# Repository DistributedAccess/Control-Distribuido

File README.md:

# Control-Distribuidos
Sistema de control de acceso distribuido por reconocimiento de patrones

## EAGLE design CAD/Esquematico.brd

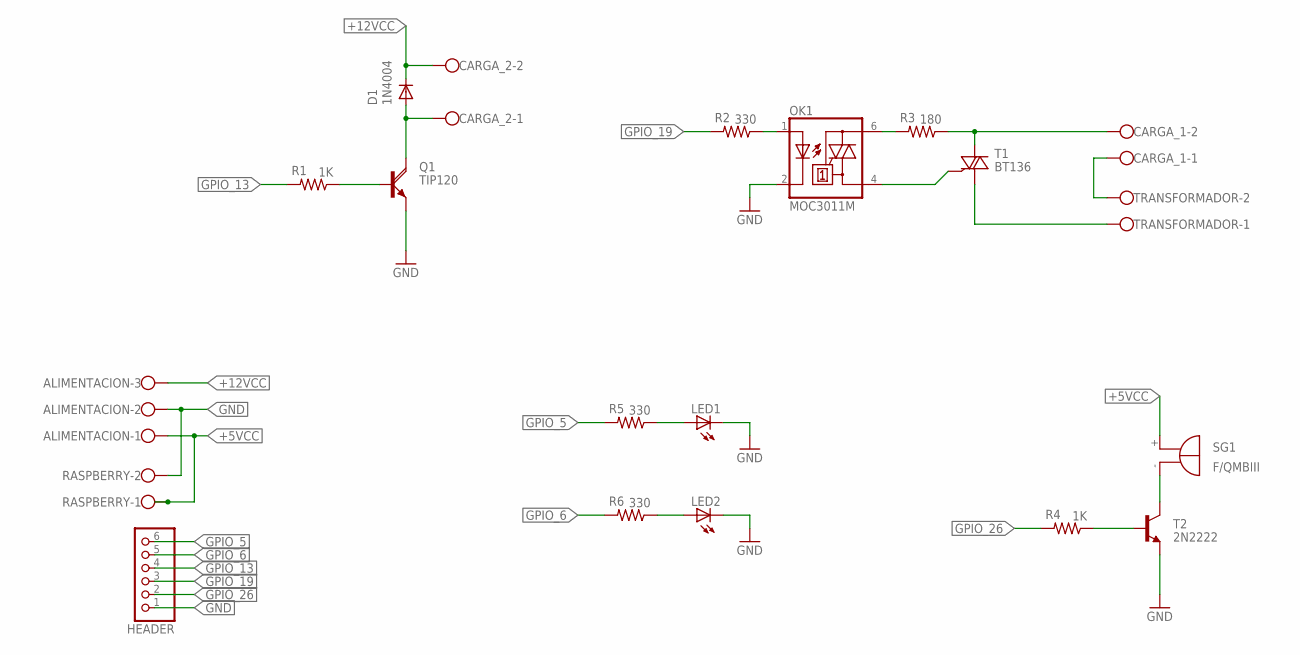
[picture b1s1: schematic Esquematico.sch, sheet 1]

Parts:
ALIMENTACION: W237-103
CARGA_1, CARGA_2: W237-102
D1: 1N4004; DO41-10
HEADER: PINHD-1X6B; 1X06-BIG
LED1, LED2: LED5MM
OK1: MOC3011M; DIL06
Q1: TIP120; TO220AH
R1, R4: 1K; 0207/10
R2, R5, R6: 330; 0207/10
R3: 180; 0207/10
RASPBERRY: W237-102
SG1: F/QMBIII
T1: BT136; TO220AB
T2: 2N2222; TO92-EBC-OVAL
TRANSFORMADOR: W237-102

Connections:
+5VCC: ALIMENTACION.1, RASPBERRY.1, SG1.+ (-)
+12VCC: ALIMENTACION.3, CARGA_2.2, D1.C
CARGA_2: CARGA_2.1, D1.A, Q1.C
GND: ALIMENTACION.2, HEADER.1, LED1.K (C), LED2.K (C), OK1.2 (C), Q1.E, RASPBERRY.2, T2.E
GPIO_5: HEADER.6, R5.2
GPIO_6: HEADER.5, R6.2
GPIO_13: HEADER.4, R1.2
GPIO_19: HEADER.3, R2.2
GPIO_26: HEADER.2, R4.2
unnamed: LED1.A, R5.1
unnamed: Q1.B, R1.1
unnamed: SG1.- (+), T2.C
unnamed: OK1.1 (A), R2.1
unnamed: OK1.6 (A2), R3.2
unnamed: CARGA_1.2, R3.1, T1.2 (A2)
unnamed: OK1.4 (A1), T1.3 (G)
unnamed: LED2.A, R6.1
unnamed: CARGA_1.1, TRANSFORMADOR.2
unnamed: T1.1 (A1), TRANSFORMADOR.1
unnamed: R4.1, T2.B

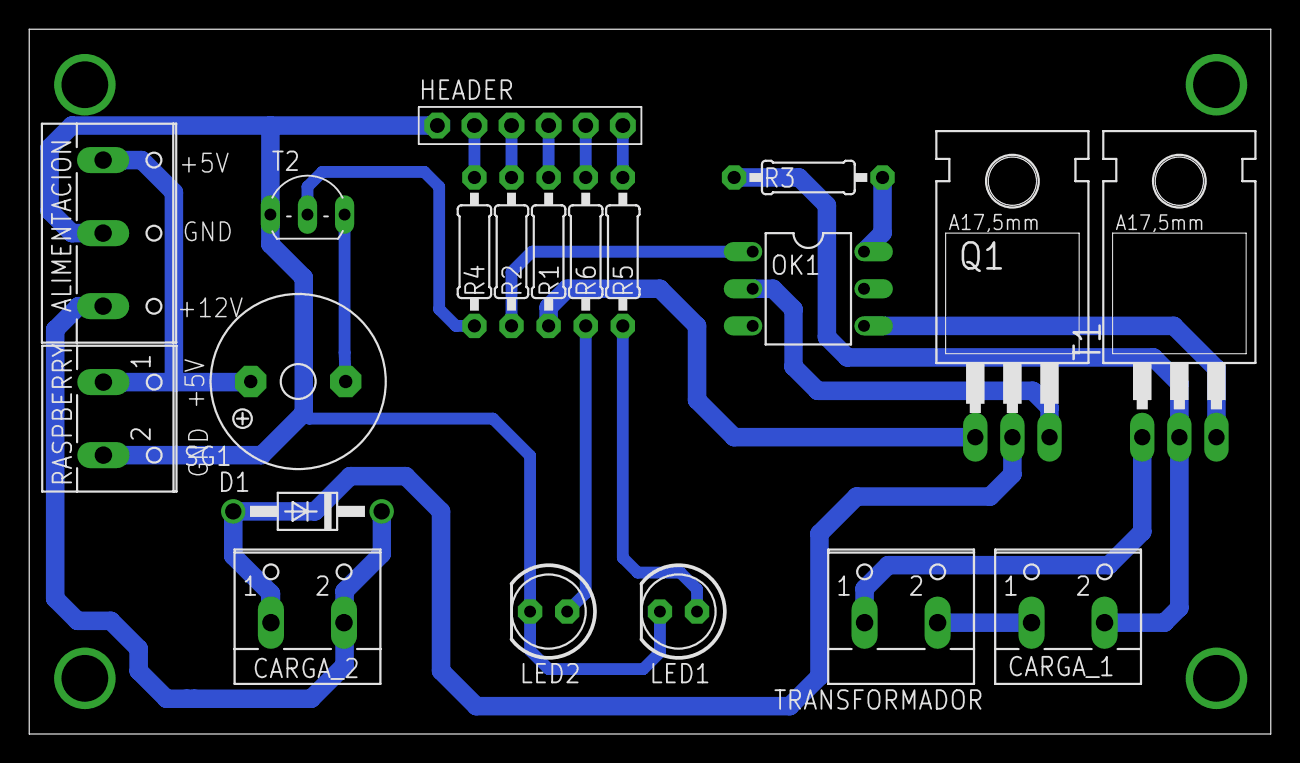
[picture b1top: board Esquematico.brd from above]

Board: 2 copper layers, 85.0 x 48.2 mm, 20 parts (0 on the bottom side), 20 nets.

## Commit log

2017-11-09 Primer Commit
2017-11-10 Segundo commit
2017-11-10 third commit
2017-11-13 Agregar Datos Listo
2017-11-13 Eliminar ajua
2017-11-13 Consultas
2017-11-13 Crear DB y Configuracion_Red Listagit add -A ajua papu
2017-11-14 Agregar Ip desde otro host programas CLiente y servidor
2017-11-14 No quiero perder este avance lo juro por Dios
2017-11-15 Otras consultas
2017-11-15 Tabla de Ruteo Lista!
2017-11-16 Registar Host Externo y regresarle la tabla de ruteo falta que el host la guarde en su BD
2017-11-16 LOGRE REPLICAR LAS BDgit add -Agit add -A
2017-11-19 Cambio de libreria a MySQLdb
2017-11-19 Cambio de libreria a MySQLdb 2
2017-11-19 Cambio de libreria a MySQLdb 3
2017-11-19 Cambio de libreria a MySQLdb 4
2017-11-19 Cambio de libreria a MySQLdb 5
2017-11-19 YA ESTA POR FINgit add -Agit add -A
2017-11-19 FALTO UN DETALLITO
2017-11-20 Creando clase Base de Datos y nuevos Cliente
2017-11-20 Actualiazacion en Base_Datos
2017-11-20 Actualiazacion en Base_Datos2
2017-11-20 pequeno bug encontrado!
2017-11-20 Bug super iper mega escondido pero reparado
2017-11-20 Ya me voy a dormir son las 4:50 AMgit add -A!
2017-11-20 PCB ok!
2017-11-26 Bases de Datos
2017-11-26 Deteccion de ERROR THE BEGININ
2017-11-26 Avances avances
2017-11-26 Consulta de Redgit add -Agit add -A
2017-11-26 Consultar Ruta 100% funcionando falta documentarlagit add -A!
2017-11-26 Primera prueba
2017-11-26 Deteccion de fallas casi
2017-11-27 Deteccion de Errores con Hilos Funciona, Falta pulirlo
2017-11-27 Actualizar BD listo!
2017-11-27 FOTOS
2017-11-27 modificacionLBP
2017-11-28 Vamo a hacer pruebas
2017-11-29 RECONOCIMIENTO
2017-11-29 BASES DE DATOS LBP CONFIGURADA!
2017-11-29 Primer prueba
2017-11-29 Correccion desde la RASPB
2017-11-30 puff
2017-11-30 bugs
2017-11-30 a vers
2017-11-30 Se me acabaron las ideas para commits :(
2017-11-30 Distancia Euclidiana Ok desde la raspberry
2017-12-01 COMMIT DESDE LA RASPBERRY ECNONTRE EL ERROOOOO1git add -Agit add -A
2017-12-01 Open cv
2017-12-01 No quiero perder esto
2017-12-01 Procesamiento
2017-12-02 asdfghjkl;
2017-12-13 Corregi algunos bugs de la Distancia Euclidiana
2017-12-14 Dist. Euclidiana con promedio Listo!
2017-12-14 Con 10mLBP
2017-12-15 Procesamiento LBP
2017-12-15 REgistr
2017-12-15 Guardar
2017-12-15 POR FIN LOGRE RECONOCER A LA GENTE DE LAS FOTOS AJUA
2017-12-15 Audios
2017-12-15 Lugs
2017-12-17 Save
2017-12-18 ALMOST
2017-12-18 Pagina WEB
